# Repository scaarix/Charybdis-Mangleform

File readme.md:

# DISCONTINUED

# Charybdis Mangleform
A fork of the Charbdis keyboard by Bastarkb

## About
A 3x6 split keyboard with magnetic removable thumb cluster and trackball

# WARNING!
This is currently in development and the case should not be printed 

# Updates

Stopped procrastinating and started to work on the case (I suck at using fusion)
---------------------------------------------------------------------------------

# Current Progress
- [x] Route PCB
- [ ] Make case
- [ ] Buy and Test PCB

# Sourcing the components

## Electronic components

Depending on which version you print, you will need more or less of each component.

The 3d files are designed around a custom sensor PCB:

https://github.com/Bastardkb/charybdis-pmw-sensor

You will need to source all of the components from the sensor PCB's BOM.

Otherwise, you can also use other sensor PCBs, but you will need to modify the 3d adapter files.

Components necessary:

| Part name                         | Amount (4x6) | Amount (3x5) | Link                                                                                       |
| --------------------------------- | ------------ | ------------ | ------------------------------------------------------------------------------------------ |
| Elite-C                           | 2            | 2            |                                                                                            |
| Elite-C adapter for the Charybdis | 2            | 2            | https://github.com/Bastardkb/Elite-C-holder                                         |
| Cables                            |              |              | 28 AWG recommended                                                                         |
| Audio jack, SMD                   | 2            | 2            |                                                                                            |
| Button, 4x4x1.5                   | 2            | 2            | https://www.aliexpress.com/item/1005001304569553.html?spm=a2g0s.9042311.0.0.27424c4dDwgcp7 |
| Sensor PCB                        | 1            | 1            | see details below                                                                          |
| Bearing, MR63-3x6x2.5mm           | 3            | 3            |                                                                                            |
| Flexible PCB for the plate (4x6)  | 2            | 0            | https://github.com/Bastardkb/Scylla-PCB-Plate                                              |
| Flexible PCB for the plate (3x5)  | 0            | 2            | https://github.com/Bastardkb/Skeletyl-PCB-plate                                            |
| Flexible PCB for the thumbs       | 1            | 1            | https://github.com/Bastardkb/PCB_thumbs_Charybdis                                          |
| Flexible PCB for the thumbs (4x6) | 1            | 0            | https://github.com/Bastardkb/Scylla-PCB-thumb-cluster                                      |
| Flexible PCB for the thumbs (3x5) | 0            | 1            | https://github.com/Bastardkb/TBK-Mini-PCB-thumb-cluster                                    |
| SOD123 Diodes                     | 8            | 35           |                                                                                            |
| BAT54C Diodes                     | 24           | 0            |                                                                                            |
| M4 8mm Torx Screw                 | 16           | 12           | Conrad                                                                                     |
| M4 screw insert, M4 X D6.0 X L5.0 | 16           | 12           | https://fr.aliexpress.com/item/4000232925592.html?spm=a2g0s.12269583.0.0.6aef4f282LZO4v    |
| Screws, M3 8mm Torx               | 8            | 8            |                                                                                            |
| Heated screw insert, M3x5x5       | 5            | 5            |                                                                                            |

If you want RGB, you will also need:

| Part name          |  Amount (3x6) | Amount        | Link       |
| ------------------ | ------        | ------------- | ---------- |
| SK6812 MINI        | 42            |               |            |
| Place Holder       |               |               |            |
| Place Holder       |               |               |            |
| Place Holder       |               |               |            |
| Place Holder       |               |               |            |             

# License 

This work is licensed under a Creative Commons Attribution-NonCommercial-ShareAlike 4.0 International License.

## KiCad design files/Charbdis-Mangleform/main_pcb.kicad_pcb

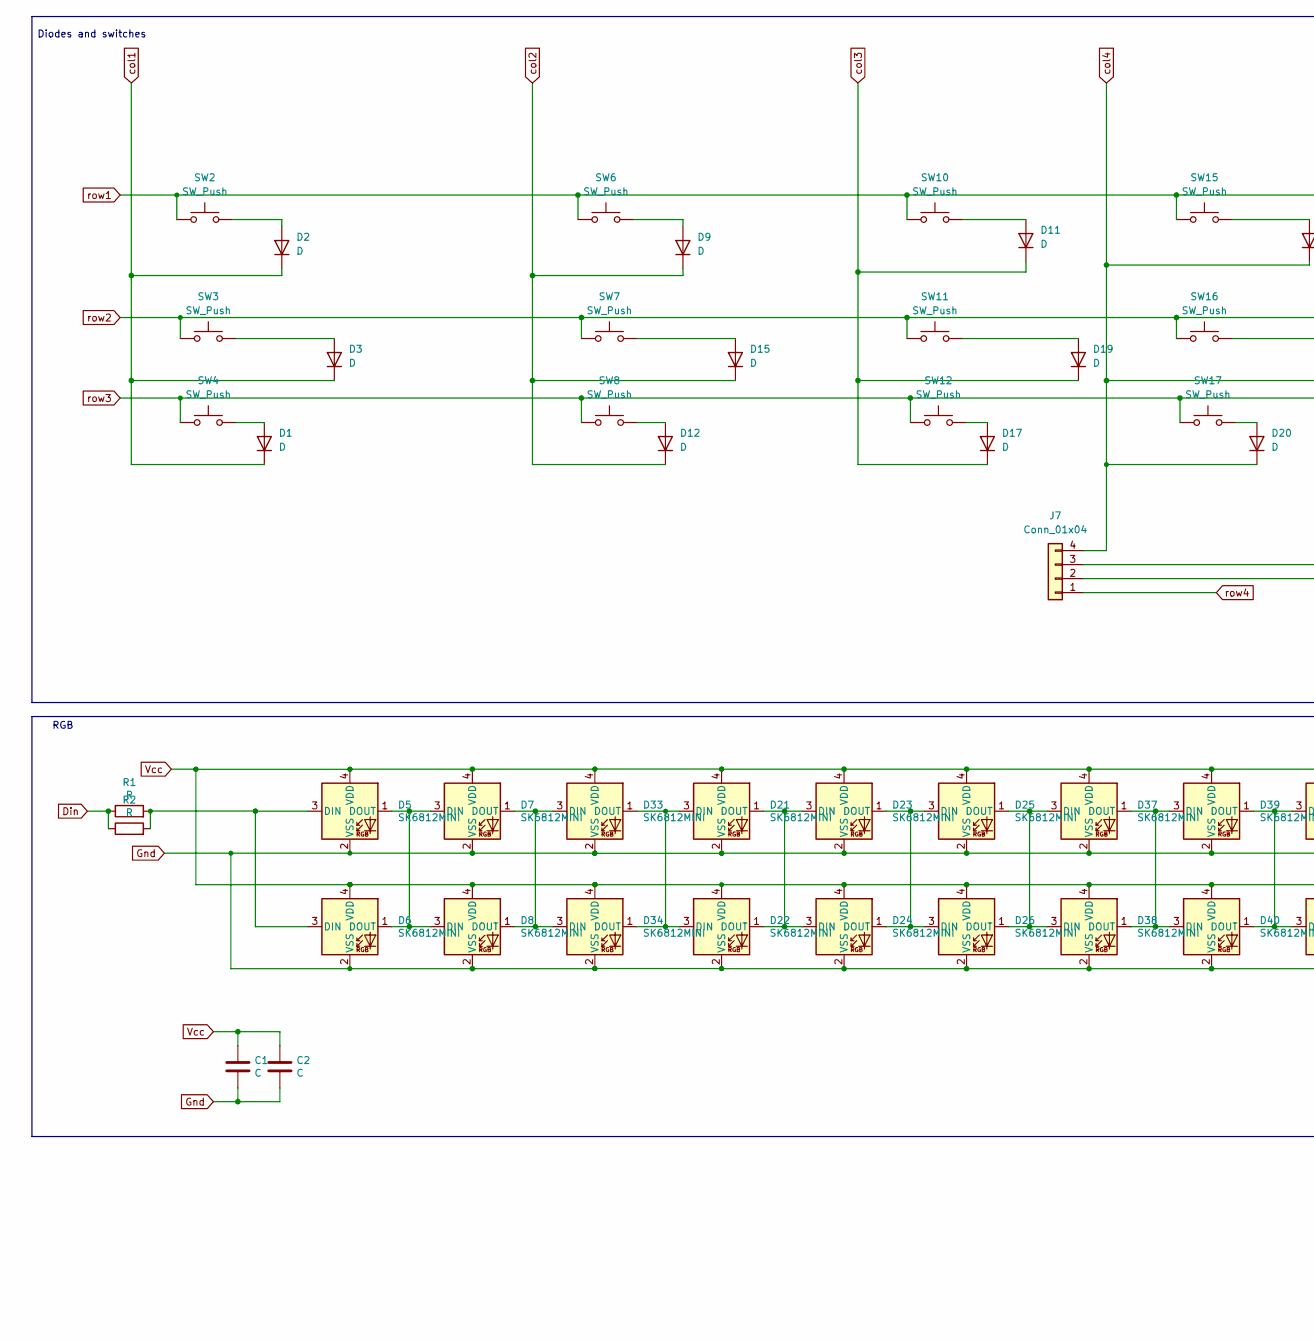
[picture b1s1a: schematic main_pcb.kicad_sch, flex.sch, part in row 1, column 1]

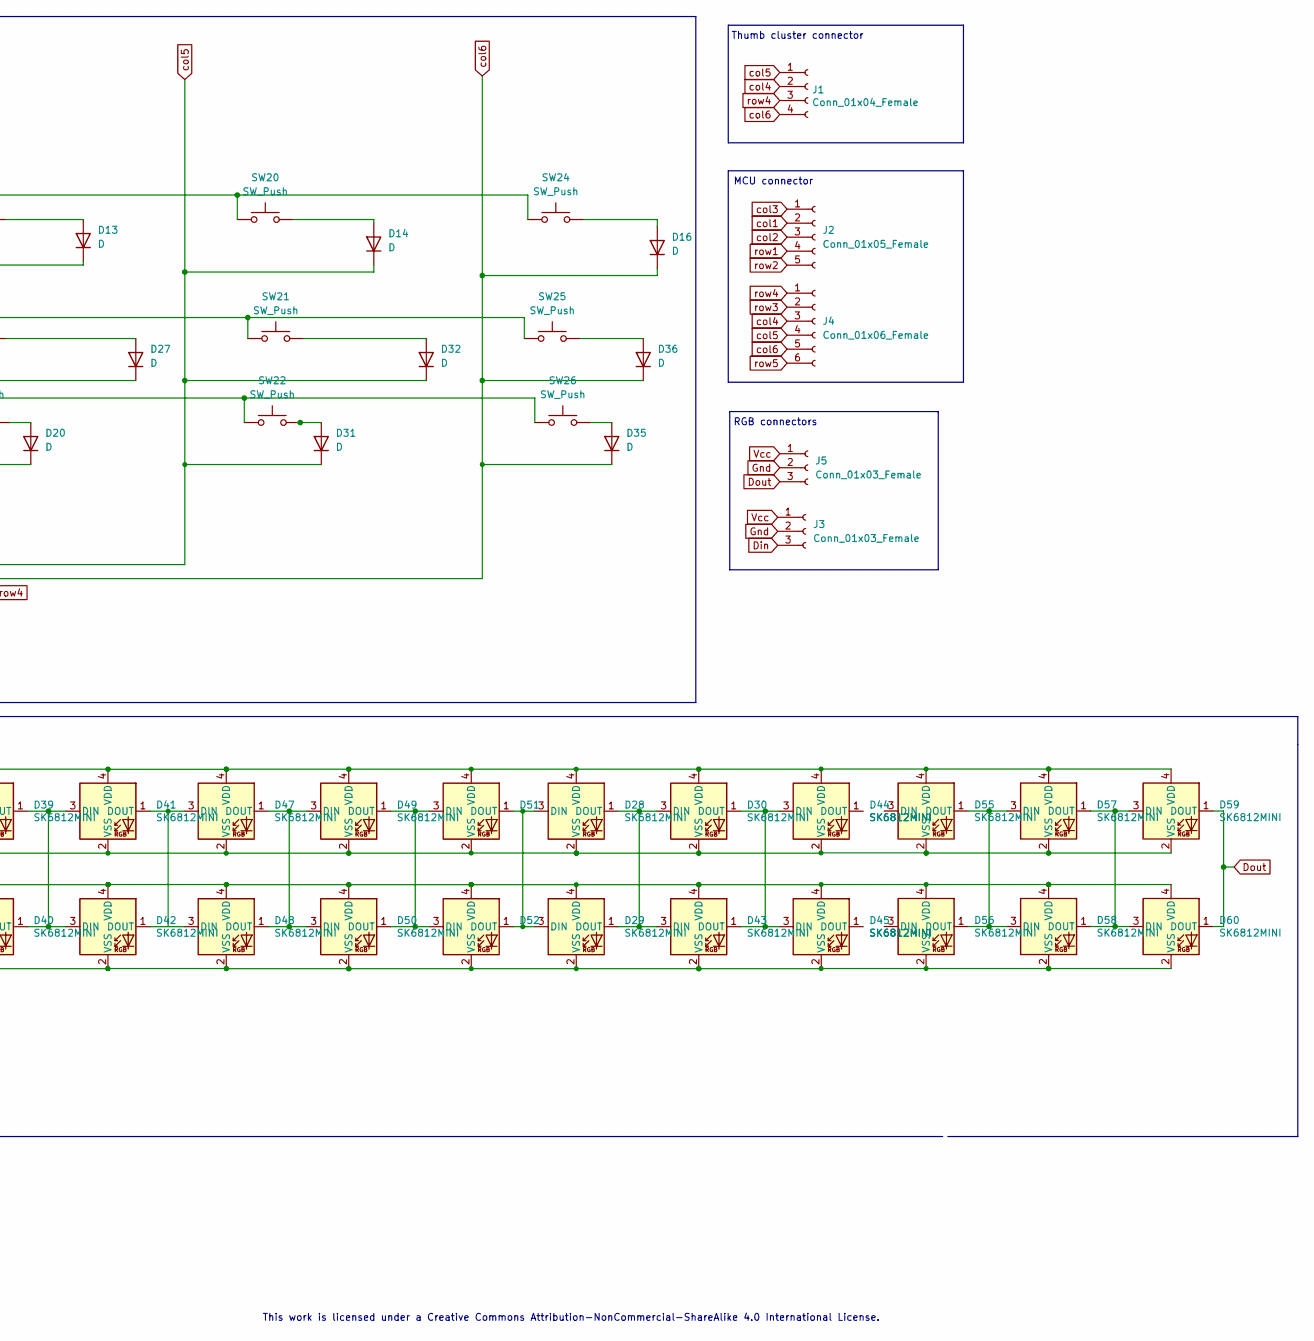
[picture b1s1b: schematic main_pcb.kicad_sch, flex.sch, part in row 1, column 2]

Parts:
C1, C2: C; C_1206_3216Metric_Pad1.42x1.75mm_HandSolder
D1, D2, D3, D9, D11, D12, D13, D14, D15, D16, D17, D19, D20, D27, D31, D32, D35, D36: D; Diode_TH_SOD123
D5, D7, D21, D23, D25, D28, D30, D33, D37, D39, D41, D44, D47, D49, D51, D55, D57, D59: SK6812MINI; YS-SK6812MINI-E_REVERSE
D6, D8, D22, D24, D26, D29, D34, D38, D40, D42, D43, D45, D48, D50, D52, D56, D58, D60: SK6812MINI; YS-SK6812MINI-E_REVERSE_NO_EDGECUT
J1: Conn_01x04_Female; PinHeader_1x04_P2.54mm_Vertical
J2: Conn_01x05_Female; PinHeader_1x05_P2.54mm_Vertical
J3, J5: Conn_01x03_Female; PinHeader_1x03_P2.54mm_Vertical
J4: Conn_01x06_Female; PinHeader_1x06_P2.54mm_Vertical
J7: Conn_01x04; 4 pin magnetic connector
R1, R2: R; R_1206_3216Metric_Pad1.42x1.75mm_HandSolder
SW2, SW3, SW4, SW6, SW7, SW8, SW10, SW11, SW12, SW15, SW16, SW17, SW20, SW21, SW22, SW24, SW25, SW26: SW_Push; SW_MX_reversible

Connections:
Din: J3.3, R1.1, R2.1
Dout: D59.1 (DOUT), D60.1 (DOUT), J5.3
Gnd: C1.2, C2.2, D5.2 (VSS), D6.2 (VSS), D7.2 (VSS), D8.2 (VSS), D33.2 (VSS), D34.2 (VSS), J3.2, J5.2
unnamed: D1.2 (A), SW4.2
unnamed: D2.2 (A), SW2.2
unnamed: D3.2 (A), SW3.2
unnamed: D5.1 (DOUT), D6.1 (DOUT), D7.3 (DIN), D8.3 (DIN)
unnamed: D5.3 (DIN), D6.3 (DIN)
unnamed: D9.2 (A), SW6.2
unnamed: D11.2 (A), SW10.2
unnamed: D12.2 (A), SW8.2
unnamed: D13.2 (A), SW15.2
unnamed: D14.2 (A), SW20.2
unnamed: D15.2 (A), SW7.2
unnamed: D16.2 (A), SW24.2
unnamed: D17.2 (A), SW12.2
unnamed: D19.2 (A), SW11.2
unnamed: D20.2 (A), SW17.2
unnamed: D21.1 (DOUT), D22.1 (DOUT), D23.3 (DIN), D24.3 (DIN)
unnamed: D21.2 (VSS), D23.2 (VSS), D25.2 (VSS), D37.2 (VSS), D39.2 (VSS), D41.2 (VSS), D47.2 (VSS), D49.2 (VSS), D51.2 (VSS)
unnamed: D21.3 (DIN), D22.3 (DIN), D33.1 (DOUT)
unnamed: D21.4 (VDD), D23.4 (VDD), D25.4 (VDD), D37.4 (VDD), D39.4 (VDD), D41.4 (VDD)
unnamed: D22.2 (VSS), D24.2 (VSS), D26.2 (VSS), D38.2 (VSS), D40.2 (VSS), D42.2 (VSS)
unnamed: D22.4 (VDD), D24.4 (VDD), D26.4 (VDD), D38.4 (VDD), D40.4 (VDD), D42.4 (VDD)
unnamed: D23.1 (DOUT), D24.1 (DOUT), D25.3 (DIN), D26.3 (DIN)
unnamed: D25.1 (DOUT), D26.1 (DOUT), D37.3 (DIN), D38.3 (DIN)
unnamed: D27.2 (A), SW16.2
unnamed: D28.1 (DOUT), D29.1 (DOUT), D30.3 (DIN), D43.3 (DIN)
unnamed: D28.2 (VSS), D30.2 (VSS), D44.2 (VSS)
unnamed: D28.3 (DIN), D29.3 (DIN), D51.1 (DOUT), D52.1 (DOUT)
unnamed: D28.4 (VDD), D30.4 (VDD), D44.4 (VDD), D47.4 (VDD), D49.4 (VDD), D51.4 (VDD)
unnamed: D29.2 (VSS), D43.2 (VSS), D45.2 (VSS), D48.2 (VSS), D50.2 (VSS), D52.2 (VSS)
unnamed: D29.4 (VDD), D43.4 (VDD), D45.4 (VDD), D48.4 (VDD), D50.4 (VDD), D52.4 (VDD)
unnamed: D30.1 (DOUT), D43.1 (DOUT), D44.3 (DIN), D45.3 (DIN)
unnamed: D31.2 (A), SW22.2
unnamed: D32.2 (A), SW21.2
unnamed: D7.1 (DOUT), D8.1 (DOUT), D33.3 (DIN), D34.3 (DIN)
unnamed: D5.4 (VDD), D7.4 (VDD), D33.4 (VDD)
unnamed: D35.2 (A), SW26.2
unnamed: D36.2 (A), SW25.2
unnamed: D37.1 (DOUT), D38.1 (DOUT), D39.3 (DIN), D40.3 (DIN)
unnamed: D39.1 (DOUT), D40.1 (DOUT), D41.3 (DIN), D42.3 (DIN)
unnamed: D41.1 (DOUT), D47.3 (DIN)
unnamed: D42.1 (DOUT), D48.3 (DIN)
unnamed: D47.1 (DOUT), D48.1 (DOUT), D49.3 (DIN), D50.3 (DIN)
unnamed: D49.1 (DOUT), D50.1 (DOUT), D51.3 (DIN), D52.3 (DIN)
unnamed: D55.1 (DOUT), D56.1 (DOUT), D57.3 (DIN), D58.3 (DIN)
unnamed: D55.2 (VSS), D57.2 (VSS), D59.2 (VSS)
unnamed: D55.4 (VDD), D57.4 (VDD), D59.4 (VDD)
unnamed: D56.2 (VSS), D58.2 (VSS), D60.2 (VSS)
unnamed: D56.4 (VDD), D58.4 (VDD), D60.4 (VDD)
unnamed: D57.1 (DOUT), D58.1 (DOUT), D59.3 (DIN), D60.3 (DIN)
unnamed: R1.2, R2.2
Vcc: C1.1, C2.1, D6.4 (VDD), D8.4 (VDD), D34.4 (VDD), J3.1, J5.1
col1: D1.1 (K), D2.1 (K), D3.1 (K), J2.2
col2: D9.1 (K), D12.1 (K), D15.1 (K), J2.3
col3: D11.1 (K), D17.1 (K), D19.1 (K), J2.1
col4: D13.1 (K), D20.1 (K), D27.1 (K), J1.2, J4.3, J7.4
col5: D14.1 (K), D31.1 (K), D32.1 (K), J1.1, J4.4, J7.3
col6: D16.1 (K), D35.1 (K), D36.1 (K), J1.4, J4.5, J7.2
row1: J2.4, SW2.1, SW6.1, SW10.1, SW15.1, SW20.1, SW24.1
row2: J2.5, SW3.1, SW7.1, SW11.1, SW16.1, SW21.1, SW25.1
row3: J4.2, SW4.1, SW8.1, SW12.1, SW17.1, SW22.1, SW26.1
row4: J1.3, J4.1, J7.1
row5: J4.6

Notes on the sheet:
RGB connectors
MCU connector
Thumb cluster connector
Diodes and switches
RGB
This work is licensed under a Creative Commons Attribution-NonCommercial-ShareAlike 4.0 International License.

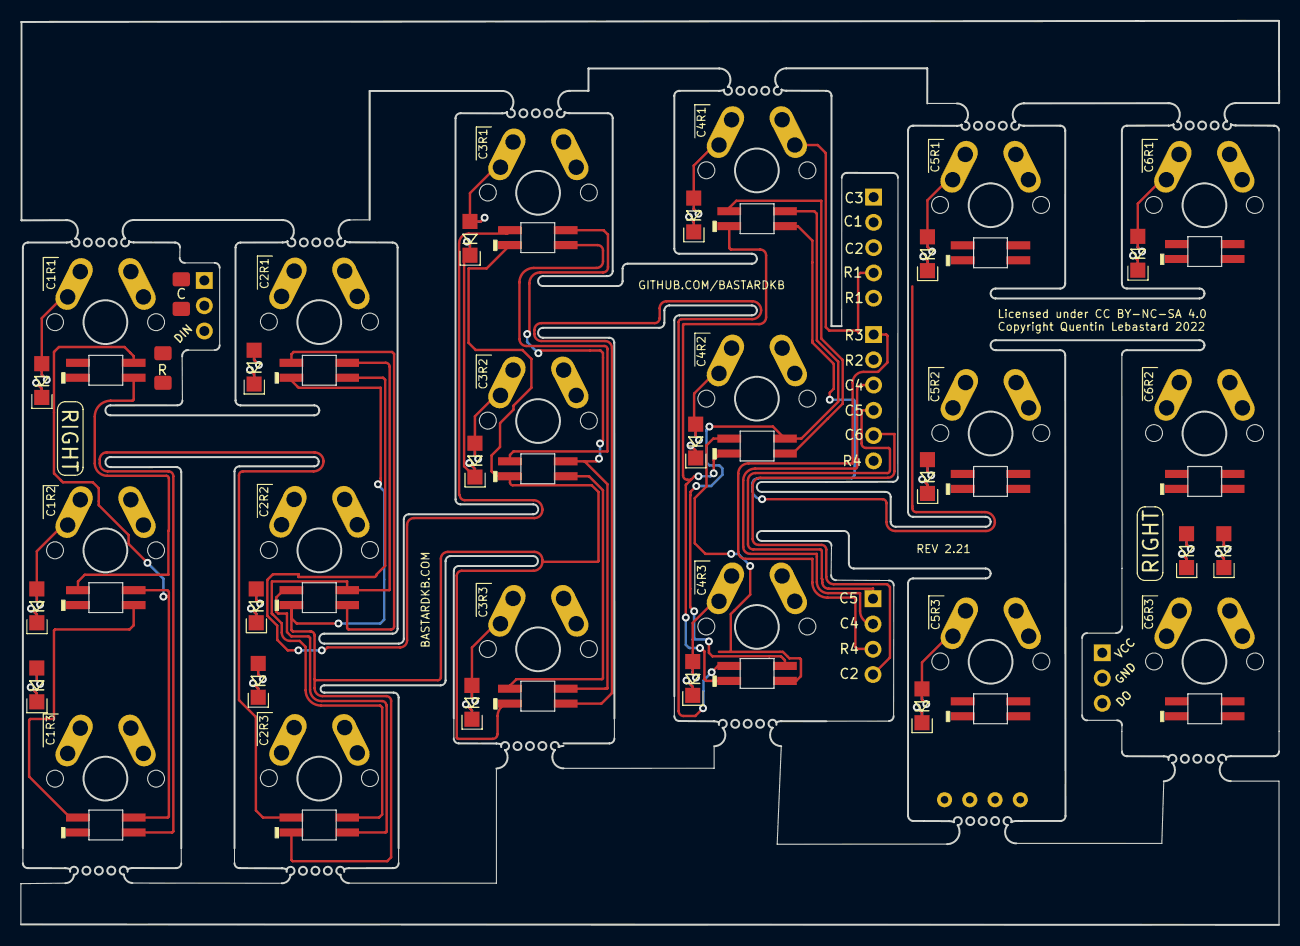
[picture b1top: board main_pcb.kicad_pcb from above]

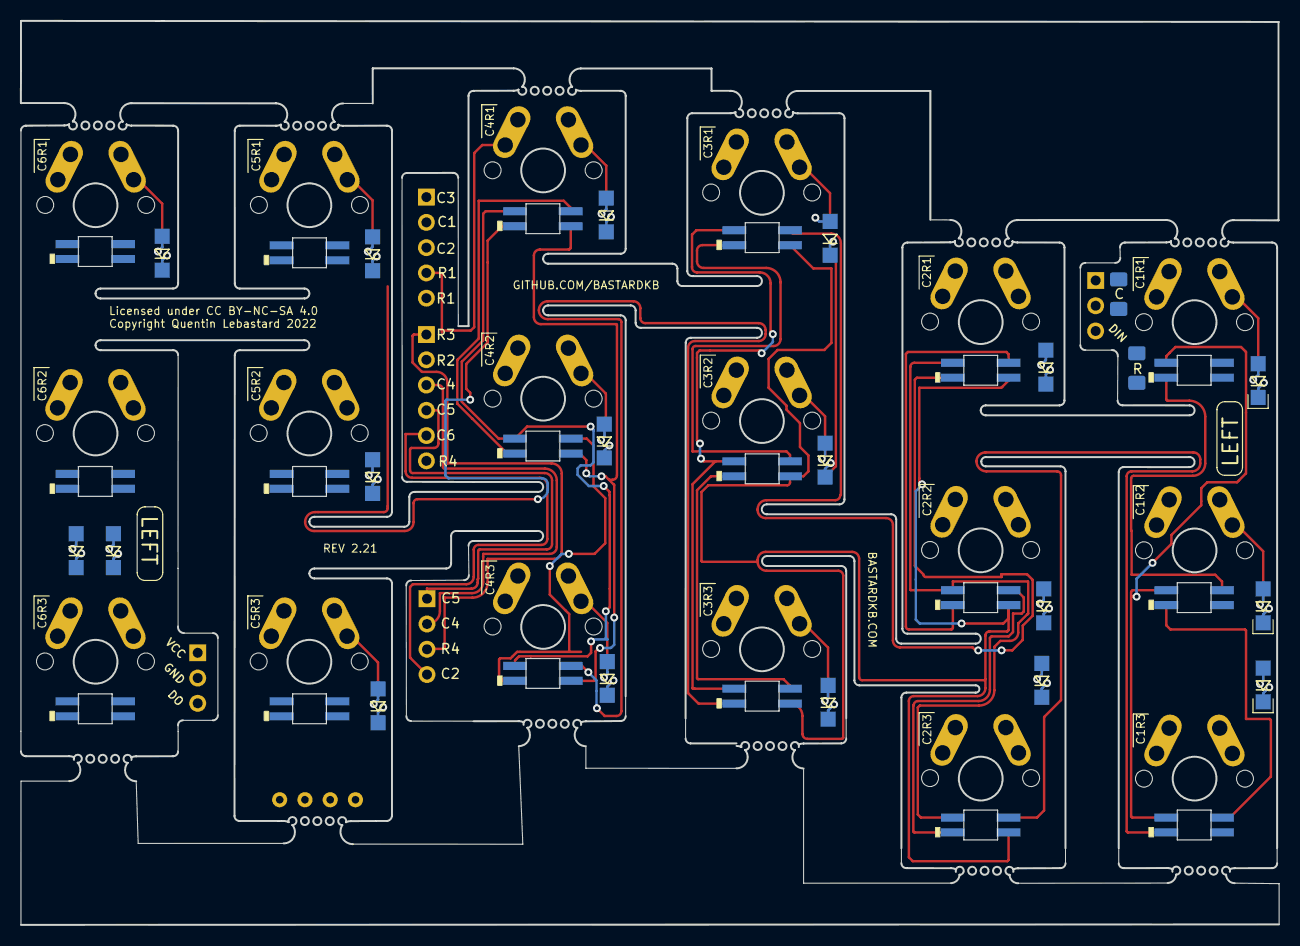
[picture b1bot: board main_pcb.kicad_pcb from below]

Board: 2 copper layers, 126.5 x 90.9 mm, 82 parts (38 on the bottom side), 64 nets.

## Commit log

2022-11-22 added main pcb
2022-12-03 routed some more (almost done one side)

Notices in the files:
files/Charbdis-Mangleform/main_pcb.kicad_pcb:
Licensed under CC BY-NC-SA 4.0
Copyright Quentin Lebastard 2022
files/Charbdis-Mangleform/main_pcb.kicad_sch:
CC BY-NC-SA 4.0
